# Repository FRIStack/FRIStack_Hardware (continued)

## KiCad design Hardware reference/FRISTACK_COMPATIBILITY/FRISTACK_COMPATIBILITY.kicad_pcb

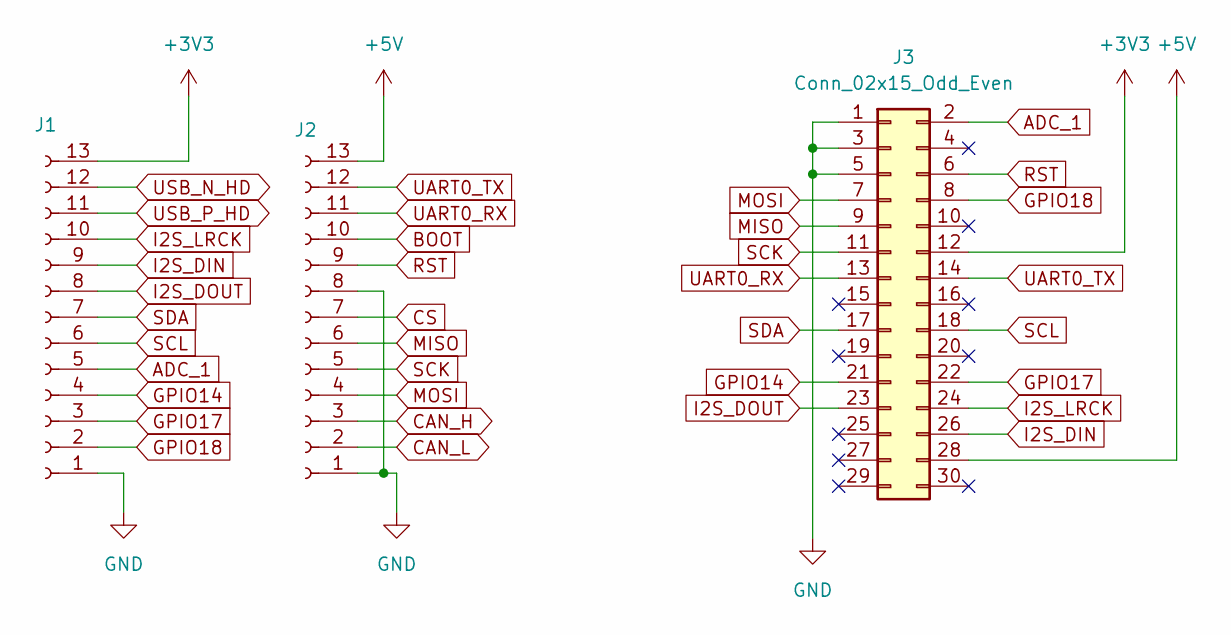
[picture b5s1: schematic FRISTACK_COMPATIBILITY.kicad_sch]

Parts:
J1, J2: Conn_01x13_Socket; PinSocket_1x13_P2.54mm_Vertical
J3: Conn_02x15_Odd_Even; PinHeader_2x15_P2.54mm_Vertical

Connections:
+3V3: J1.13, J3.12
+5V: J2.13, J3.28
ADC_1: J1.5, J3.2
BOOT: J2.10
CAN_H: J2.3
CAN_L: J2.2
CS: J2.7
GND: J1.1, J2.1, J2.8, J3.1, J3.3, J3.5
GPIO14: J1.4, J3.21
GPIO17: J1.3, J3.22
GPIO18: J1.2, J3.8
I2S_DIN: J1.9, J3.26
I2S_DOUT: J1.8, J3.23
I2S_LRCK: J1.10, J3.24
MISO: J2.6, J3.9
MOSI: J2.4, J3.7
RST: J2.9, J3.6
SCK: J2.5, J3.11
SCL: J1.6, J3.18
SDA: J1.7, J3.17
UART0_RX: J2.11, J3.13
UART0_TX: J2.12, J3.14
USB_N_HD: J1.12
USB_P_HD: J1.11

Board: 2 copper layers, 3 parts (0 on the bottom side), 18 nets, no tracks yet.

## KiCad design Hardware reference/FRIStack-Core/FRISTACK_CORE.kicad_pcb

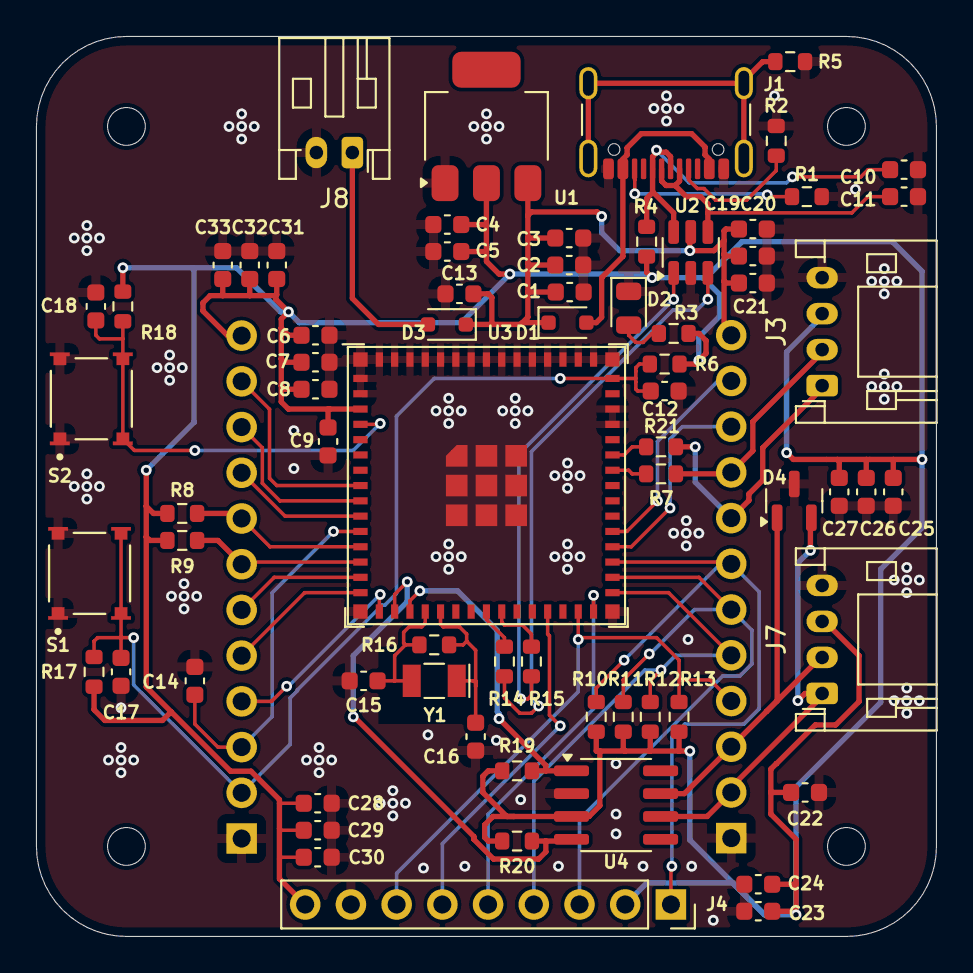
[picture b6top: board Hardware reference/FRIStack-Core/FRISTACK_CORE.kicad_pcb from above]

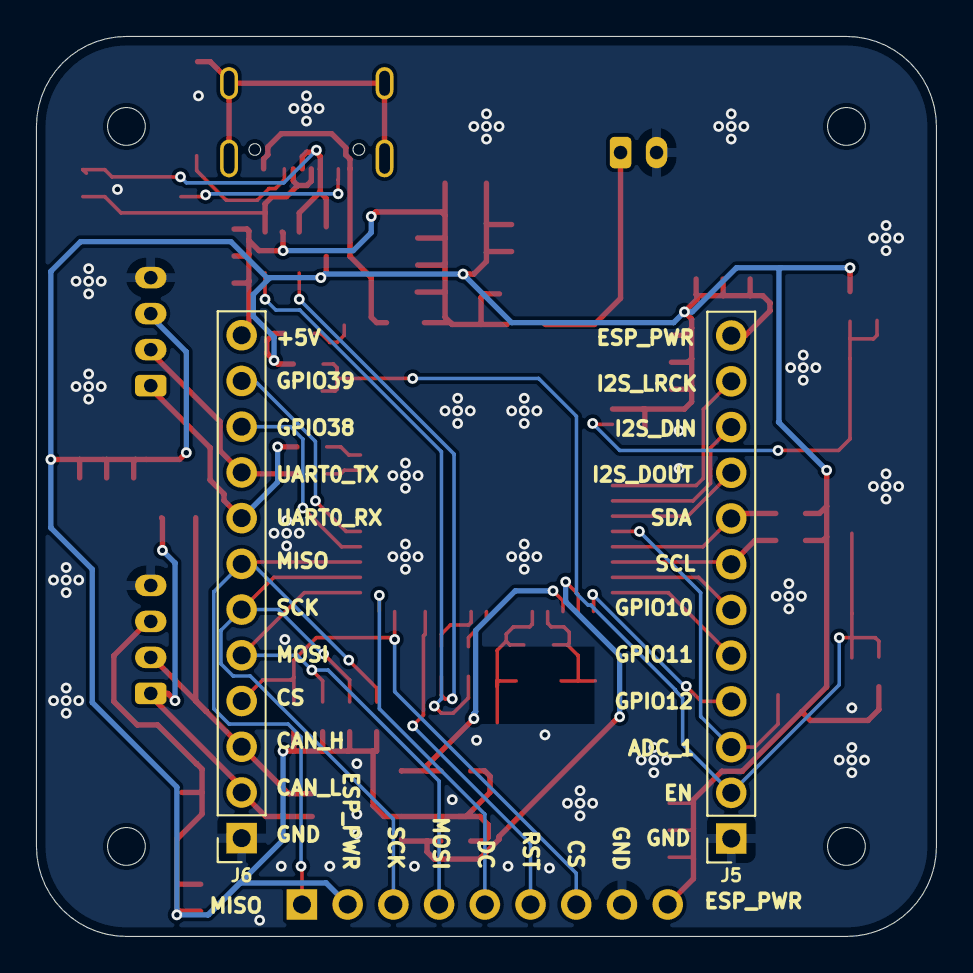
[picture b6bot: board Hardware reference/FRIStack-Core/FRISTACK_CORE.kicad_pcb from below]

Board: 2 copper layers, 50.0 x 50.0 mm, 72 parts (2 on the bottom side), 44 nets.

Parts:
C1, C10, C11: 10uf; C_0603_1608Metric
C2, C5: 10uF; C_0603_1608Metric
C3, C4, C14, C17, C18: 0.1uF; C_0603_1608Metric
C6, C13: 22uF; C_0603_1608Metric
C7, C20, C23, C26, C29, C32: 100nF; C_0603_1608Metric
C8, C21, C24, C27, C30, C33: 1nF; C_0603_1608Metric
C9: 100pF; C_0603_1608Metric
C12: 1uF; C_0603_1608Metric
C15, C16: 15pF; C_0603_1608Metric
C19, C22, C25, C28, C31: 2.2uF; C_0603_1608Metric
D1, D3: 1N5819WS; D_SOD-323
D2: LED RED; LED_0805_2012Metric
D4: PESD1CAN; SOT-23
J1: USB_C_Receptacle_USB2.0_16P; USB_C_Receptacle_GCT_USB4105-xx-A_16P_TopMnt_Horizontal
J3, J7: Conn_01x04_Pin; JST_PH_S4B-PH-K_1x04_P2.00mm_Horizontal
J4: Conn_01x09_Socket; PinSocket_1x09_P2.54mm_Vertical
J5, J6: Conn_01x12_Socket; PinSocket_1x12_P2.54mm_Vertical
J8: Conn_01x02_Pin; JST_PH_S2B-PH-K_1x02_P2.00mm_Horizontal
R1, R2: 5.1K; R_0603_1608Metric
R3: 75; R_0603_1608Metric
R4, R6, R10, R11, R12, R13, R17, R18: 10K; R_0603_1608Metric
R5: 1M; R_0603_1608Metric
R7: 499; R_0603_1608Metric
R8, R9: 2K2; R_0603_1608Metric
R14, R15, R21: 0; R_0603_1608Metric
R16: ?; R_0603_1608Metric
R19, R20: 4K7; R_0603_1608Metric
S1, S2: TL3315NF100Q; SW_TL3315NF100Q
U1: AZ1117-3.3; SOT-223
U2: USBLC6-2SC6; SOT-23-6
U3: ESP32-S3-MINI-1U
U4: SN65HVD232; SOIC-8_3.9x4.9mm_P1.27mm
Y1: 32.768 kHz; Crystal_SMD_G8-2Pin_3.2x1.5mm

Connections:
+5V: C1.1, C2.1, C3.1, C13.1, C19.1, C20.1, C21.1, D1.1 (K), D3.1 (K), J6.12, U1.3 (VI), U2.5 (VBUS)
ADC_1: C14.1, J5.3, U3.11 (IO7)
CAN_D: R19.1, U3.18 (IO14), U4.1 (D)
CAN_H: D4.1 (K), J6.3, J7.2, U4.7 (CANH)
CAN_L: D4.2 (K), J6.2, J7.1, U4.6 (CANL)
CAN_R: R20.2, U3.17 (IO13), U4.4 (R)
CS: J4.7, J6.4, R13.1, U3.29 (IO34)
DC: J4.5, U3.30 (IO48)
EN: C12.1, C17.1, J5.2, R6.2, R17.2, S1.3, S1.4, U3.45 (EN)
ESP_PWR: C4.1, C5.1, C6.1, C7.1, C8.1, C9.1, C22.1, C23.1, C24.1, C25.1, C26.1, C27.1, C28.1, C29.1, C30.1, C31.1, C32.1, C33.1, J3.3, J4.2, J4.9, J5.12, J7.3, R3.1, R4.2, R6.1, R8.2, R9.2, R10.2, R11.2, R12.2, R13.2, R17.1, R18.1, R19.2, R20.1, U1.2 (VO), U3.3 (3V3), U4.3 (VCC)
GND: C1.2, C2.2, C3.2, C4.2, C5.2, C6.2, C7.2, C8.2, C9.2, C10.2, C11.2, C12.2, C13.2, C14.2, C15.1, C16.1, C17.2, C18.2, C19.2, C20.2, C21.2, C22.2, C23.2, C24.2, C25.2, C26.2, C27.2, C28.2, C29.2, C30.2, C31.2, C32.2, C33.2, D2.1 (K), D4.3 (A), J1.A1 (GND), J1.A12 (GND), J1.B1 (GND), J1.B12 (GND), J3.4, J4.8, J5.1, J6.1, J7.4, J8.2, R1.1, R2.2, R5.2, S1.1, S1.2, S2.1, S2.2, U1.1 (GND), U2.2 (GND), U3.1 (GND), U3.2 (GND), U3.42 (GND), U3.43 (GND), U3.46 (GND), U3.47 (GND), U3.48 (GND), U3.49 (GND), U3.50 (GND), U3.51 (GND), U3.52 (GND), U3.53 (GND), U3.54 (GND), U3.55 (GND), U3.56 (GND), U3.57 (GND), U3.58 (GND), U3.59 (GND), U3.60 (GND), U3.61 (GND), U3.62 (GND), U3.63 (GND), U3.64 (GND), U3.65 (GND), U4.2 (GND)
GPIO0: C18.1, R18.2, S2.3, S2.4, U3.4 (IO0)
GPIO10: J5.6, U3.14 (IO10)
GPIO11: J5.5, U3.15 (IO11)
GPIO12: J5.4, U3.16 (IO12)
GPIO38: J6.10, U3.34 (IO38)
GPIO39: J6.11, U3.35 (IO39)
I2S_DIN: J5.10, U3.9 (IO5)
I2S_DOUT: J5.9, U3.10 (IO6)
I2S_LRCK: J5.11, U3.8 (IO4)
MISO: J4.1, J6.7, R10.1, U3.33 (IO37)
MOSI: J4.4, J6.5, R12.1, U3.31 (IO35)
unnamed: D1.2 (A), J1.A4 (VBUS), J1.A9 (VBUS), J1.B4 (VBUS), J1.B9 (VBUS)
unnamed: D2.2 (A), R3.2
unnamed: D3.2 (A), J8.1
unnamed: J1.A5 (CC1), R2.1
unnamed: J1.B5 (CC2), R1.2
unnamed: J1.S1 (SHIELD), R5.1
unnamed: R21.1, U3.40 (RXD0)
unnamed: R7.1, U3.39 (TXD0)
unnamed: R15.1, U3.24 (USB_D+)
unnamed: R14.1, U3.23 (USB_D-)
RST_LCD: J4.6, U3.27 (IO47)
SCK: J4.3, J6.6, R11.1, U3.32 (IO36)
SCL: J5.7, R9.1, U3.13 (IO9)
SDA: J5.8, R8.1, U3.12 (IO8)
UART0_RX: J3.1, J6.8, R21.2
UART0_TX: J3.2, J6.9, R7.2
USB_DN: C11.1, J1.A7 (D-), J1.B7 (D-), U2.4 (I/O2)
USB_DN_2: R14.2, U2.3 (I/O2)
USB_DP: C10.1, J1.A6 (D+), J1.B6 (D+), R4.1, U2.6 (I/O1)
USB_DP_2: R15.2, U2.1 (I/O1)
X_TAL_N: C16.2, R16.1, U3.20 (IO16), Y1.1
X_TAL_P: C15.2, R16.2, U3.19 (IO15), Y1.2

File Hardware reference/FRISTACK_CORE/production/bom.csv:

Designator,Footprint,Quantity,Value,LCSC Part #
"C1, C2, C5",0603,3,10uf,
C12,0603,1,1uF,
"C13, C6",0603,2,22uF,
"C14, C17, C18, C3, C4",0603,5,0.1uF,
"C15, C16",0603,2,15pF,
"C19, C22, C25, C28, C31",0603,5,2.2uF,
"C20, C23, C26, C29, C32, C7",0603,6,100nF,
"C21, C24, C27, C30, C33, C8",0603,6,1nF,
C9,0603,1,100pF,
"D1, D3",D_SOD-323,2,1N5819WS,
D2,0805,1,LED RED,
D4,SOT-23,1,PESD1CAN,
J1,USB_C_Receptacle_GCT_USB4105-xx-A_16P_TopMnt_Horizontal,1,USB_C_Receptacle_USB2.0_16P,
"J3, J7",JST_PH_S4B-PH-K_1x04_P2.00mm_Horizontal,2,Conn_01x04_Pin,
J4,PinSocket_1x09_P2.54mm_Vertical,1,Conn_01x09_Socket,
"J5, J6",PinSocket_1x12_P2.54mm_Vertical,2,Conn_01x12_Socket,
J8,JST_PH_S2B-PH-K_1x02_P2.00mm_Horizontal,1,Conn_01x02_Pin,
"R1, R2",0603,2,5.1K,
"R10, R11, R12, R13, R17, R18, R4, R6",0603,8,10K,
"R14, R15, R21",0603,3,0,
"R19, R20",0603,2,4K7,
R3,0603,1,75,
R5,0603,1,1M,
R7,0603,1,499,
"R8, R9",0603,2,2K2,
"S1, S2",SW_TL3315NF100Q,2,TL3315NF100Q,
U1,SOT-223,1,AZ1117-3.3,
U2,SOT-23-6,1,USBLC6-2SC6,
U3,ESP32-S3-MINI-1U,1,ESP32-S3-MINI-1U,
U4,SOIC-8_3.9x4.9mm_P1.27mm,1,SN65HVD232,
Y1,Crystal_SMD_G8-2Pin_3.2x1.5mm,1,32.768 kHz,

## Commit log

2025-02-13 Creation of project
2025-02-13 Readme
2025-02-28 Updated hardware reference
2025-03-23 first version of battery module
    started battery module project with TPS61200DRC Switching Voltage Regulators
2025-03-23 Create I2C_Test
    simple i2c scan for devices. I used ENS160 + AHT21. Devices found at address 0x38 and 0x53.Next goal is to read values from this sensors
2025-03-31 Git rework
2025-03-31 Added Core hardware reference
2025-04-14 Updated CORE schematic and PCB design
2025-07-07 Added SENSOR-NODE and reworked CORE
2025-07-07 Updated .gitignore
2025-07-08 Repository cleanup
2025-07-28 Power management changes on CORE and SENSOR_NODE
2025-08-09 Added logos, annotations
2025-08-12 First version of IOT board
    Not completed yet. Next version will be uploaded after check.
2025-09-01 FRISTACK_IOT_v2
    Second version of iot board
2025-09-01 Cleaning
2025-09-06 IOT board v3
    Switched esp chip with sd card adapter. Replaced 120ohm termination with split termination for TWAI
2025-09-06 git ignore update
2025-09-06 gitignore update
2025-09-12 Added USBSwitch to Core and added first version of Compatibility
2025-09-22 Reworked CORE and adjusted header pins
    Added USB switch and MCP73871 for charging battery and powering the system. Changed GPIO14 to BAT, dedicated for battery.
2025-10-04 Changed jumpers with DIP switches and adjusted copper areas
2025-10-07 changed mouting holes
2025-10-16 review and new BATTERY board
    IOT - changed twai termination from header to switch option, new holes , added power planes
    SENSOR NODE - new holes and back silk text
    CORE - vertical twai termination header changed to horizontal
2025-11-28 Changes to Core and Sensor Node
